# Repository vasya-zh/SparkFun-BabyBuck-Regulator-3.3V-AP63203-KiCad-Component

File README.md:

# SparkFun-BabyBuck-Regulator-3.3V-AP63203-KiCad-Component
 SparkFun BabyBuck Regulator Breakout - 3.3V (AP63203) - KiCad version and component
 https://www.sparkfun.com/products/18357

I rebuild the SparkFun BabyBuck 3.3V Regulator PCB based on AP63203 with KiCad to create a 3d model and use it as a components for my solder kits and prototyping.

The original Eagle project from SparkFun: https://github.com/sparkfun/Buck_Regulator_AP63203

In kicad folder you can find the schematics and the board

In SparkFun-BabyBuck-3.3V.pretty you can find the footprint and a 3d-model

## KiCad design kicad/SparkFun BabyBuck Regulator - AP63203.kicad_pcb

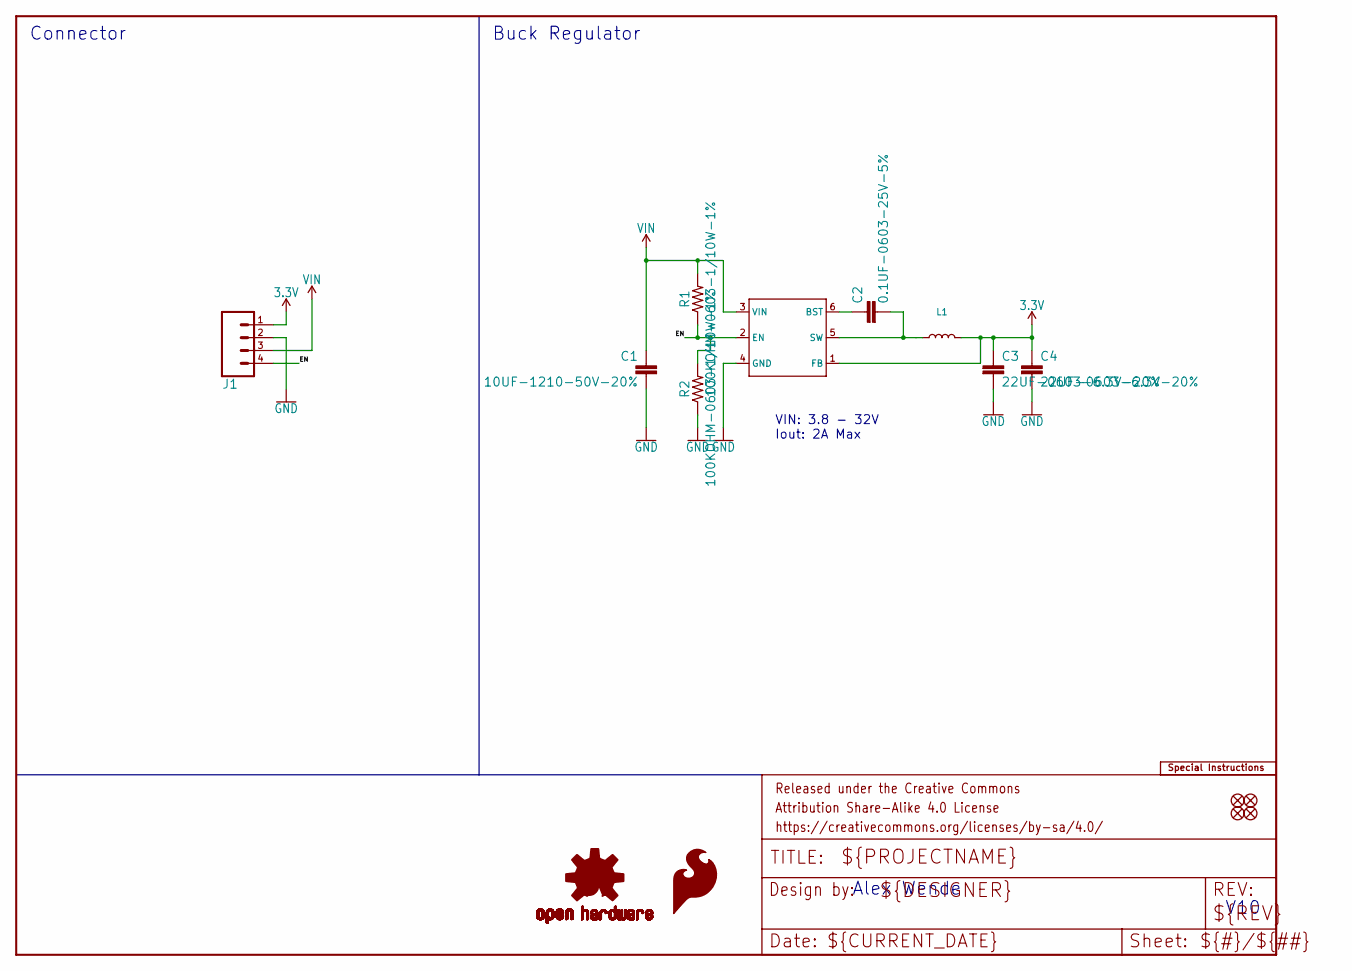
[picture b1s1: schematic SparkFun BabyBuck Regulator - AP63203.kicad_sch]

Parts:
C1: 10UF-1210-50V-20%; C_1210_3225Metric
C2: 0.1UF-0603-25V-5%; C_0603_1608Metric
C3, C4: 22UF-0603-6.3V-20%; C_0603_1608Metric
FD1, FD2, FD3, FD4: FIDUCIAL0.2MM; FIDUCIAL-0.2MM
FRAME1: FRAME-LETTER; CREATIVE_COMMONS
J1: CONN_041X04_NO_SILK; PinHeader_1x04_P2.54mm_Vertical
L1: 4.7μH_SHIELDED_INDUCTORNPIS_LS; L_Sunlord_SWPA4030S
LOGO1: SFE_LOGO_FLAME.1_INCH; SFE_LOGO_FLAME_.1
LOGO2: OSHW-LOGOS; OSHW-LOGO-S
LOGO3: SPECIAL_INSTRUCTIONS-ORDERING; ORDERING_INSTRUCTIONS
R1, R2: 100KOHM-0603-1/10W-1%; R_0603_1608Metric
U1: AP63203; TSOT-23-6

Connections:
3.3V: C3.1, C4.1, J1.1, L1.2, U1.1 (FB)
/EN: J1.4, R1.1, R2.2, U1.2 (EN)
GND: C1.2, C3.2, C4.2, J1.2, R2.1, U1.4 (GND)
unnamed: C2.1, U1.6 (BST)
unnamed: C2.2, L1.1, U1.5 (SW)
VIN: C1.1, J1.3, R1.2, U1.3 (VIN)

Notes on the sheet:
Buck Regulator
Alex Wende
VIN: 3.8 - 32V Iout: 2A Max
V10
Connector

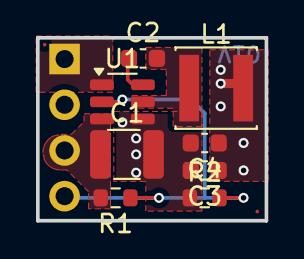
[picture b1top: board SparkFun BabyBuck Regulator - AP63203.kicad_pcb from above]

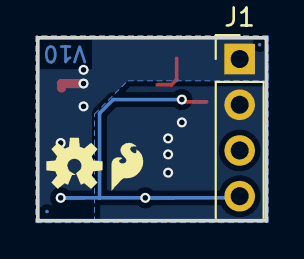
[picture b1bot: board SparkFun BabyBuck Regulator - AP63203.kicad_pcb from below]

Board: 2 copper layers, 12.7 x 10.2 mm, 17 parts (5 on the bottom side), 6 nets.

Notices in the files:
kicad/SparkFun BabyBuck Regulator - AP63203.kicad_sch:
https://creativecommons.org/licenses/by-sa/4.0
Released under the Creative Commons
parts and their libraries:
Released under the Creative Commons Attribution Share-Alike 4.0 License
